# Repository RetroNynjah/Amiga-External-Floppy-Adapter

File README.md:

# Retro Ninja Amiga external floppy adapter
An adapter that allows external connection of Shugart floppy disk drives or Gotek floppy emulators

This adapter has been tested with various Amiga floppy drives and Gotek floppy emulators.
It was designed to plug directly into the external floppy port of the Amiga and connect a Gotek USB emulator with a 34-pin IDC cable and a power cable. The floppy connector on the board is rotated so a floppy cable can go in a straight loop to a Gotek laying on top of the Amiga.
It should also be possible to mount the adapter in an external case but the floppy cable would have to be turned 180 degrees to match the connectors of the board and a Gotek.

J1 is the male 23 pin D-sub connector that plugs into the external drive port on the amiga. Pretty hard to find these today but it looks like new ones will be manufactured soon.

J2 is a male header for connecting the floppy cable. Connector can be straight or right angle, open or walled depending on what you got and what you want.

J3 is for floppy power connector. Cables can be soldered directly to board if needed.

J4 is the passthrough connector for a second or third external drive.  
Connect first row of pins on header (1...23) to first row of pins on female D-sub (1...12).  
Connect second row of pins on header (2...22) to the second row of pins on female D-sub (13...23).  

This design was based on information gathered from Amiga System Programmer's Guide by Abacus and from the scematics for the A1020 drive.  
Designed using Fusion 360. Gerber files and Eagle schematics included.

This is the third version of the board. The only new functionality from earlier versions is the added power switch/jumper. Other changes are that IC1 has been changed from 74LS00 to 74LS38, the power connector has been rotated to allow a right angle connector and silkscreen has been updated.

## BOM
 |Component|Pcs |Name|Comment|
 |:--------|---:|:---|:------|
 | 74LS38 Quad NAND | 1 | IC1 | 74F38 works and 74LS03/74HCT03 seems to work too. 74LS26 and variants of it might work. 74LS00 works partially |
 | 74LS74 Flip-Flop | 1 | IC2 | 74HCT74 works fine | 
 | 100nF ceramic capacitor | 2 | C1, C2 ||
 | 1k resistor | 4 | R1, R2, R3, R4 ||
 | 12k resistor | 1 | R5 ||
 | D-sub 23M connector | 1 | J1 | D-sub This connector is pretty hard to source at the moment. Try eBay |
 | 34-pin male header | 1 | J2 | 2x17 pin 2.54mm pitch. For floppy cable IDC connector |
 | 4 pin header | 1 | J3 | 2.54mm pitch. For floppy power cable connector (or solder cables directly to board) |
 | 24-pin header | 1 | J4 | 2x12 pin 2.54mm pitch header for outgoing connection to next drive in chain. For example IDC to DB23F. D-sub 23F connectors were manufactured by Unicorns and can't be found today |
 | Jumper | 1 | JP1 | Optional jumper or connection for a power switch. If you don't need a power jumper/switch - just leave it and bridge the solder jumper SJ1 instead |

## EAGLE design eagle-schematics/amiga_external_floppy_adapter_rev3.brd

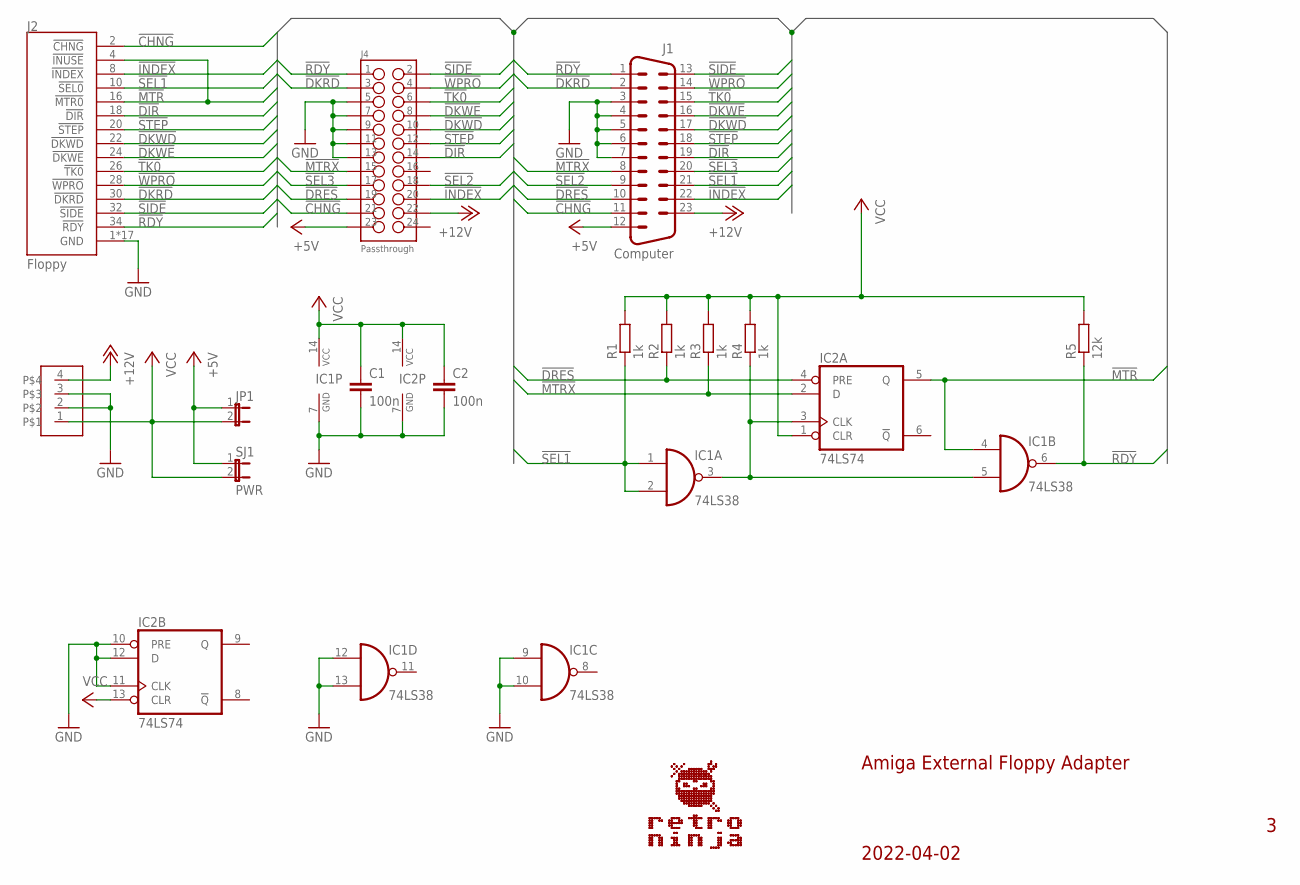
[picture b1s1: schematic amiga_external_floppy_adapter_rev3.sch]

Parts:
C1, C2: 100n; CAP_5MM_2.5X5.0_ROUND
IC1: 74LS38; DIL14
IC2: 74LS74; DIL14
J1: Computer; DSUB_M23D
J2: Floppy; HEADER_2X17_WALLED
J3: HEADER_1X4_2.50MM_RIGHT; HEADER_1X4_2.50_RIGHT
J4: Passthrough; HEADER_2X12_WALLED
JP1: JUMPER-2; HEADER_1X2
R1, R2, R3, R4: 1k; 0207/10
R5: 12k; 0207/10
SJ1: PWR; SJ-2

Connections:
!CHNG: J1.11, J2.2 (!CHNG), J4.21
!DIR: J1.19, J2.18 (!DIR), J4.14
!DKRD: J1.2, J2.30 (!DKRD), J4.3
!DKWD: J1.17, J2.22 (!DKWD), J4.10
!DKWE: J1.16, J2.24 (!DKWE), J4.8
!DRES: IC2.4 (PRE), J1.10, J4.19, R2.1
!INDEX: J1.22, J2.8 (!INDEX), J4.20
!MTR: IC1.4 (I0), IC2.5 (Q), J2.4 (!INUSE), J2.16 (!MTR0)
!MTRX: IC2.2 (D), J1.8, J4.15, R3.1
!RDY: IC1.6 (O), J1.1, J2.34 (!RDY), J4.1, R5.1
!SEL1: IC1.1 (I0), IC1.2 (I1), J1.21, J2.10 (!SEL0), R1.1
!SEL2: J1.9, J4.18
!SEL3: J1.20, J4.17
!SIDE: J1.13, J2.32 (!SIDE), J4.2
!STEP: J1.18, J2.20 (!STEP), J4.12
!TK0: J1.15, J2.26 (!TK0), J4.6
!WPRO: J1.14, J2.28 (!WPRO), J4.4
+5V: J1.12, J4.23, JP1.1, SJ1.1
+12V: J1.23, J3.4, J4.22
GND: C1.2, C2.2, IC1.7 (GND), IC1.9 (I0), IC1.10 (I1), IC1.12 (I0), IC1.13 (I1), IC2.7 (GND), IC2.10 (PRE), IC2.11 (CLK), IC2.12 (D), J1.3, J1.4, J1.5, J1.6, J1.7, J2.1 (GND), J2.3 (GND), J2.5 (GND), J2.7 (GND), J2.9 (GND), J2.11 (GND), J2.13 (GND), J2.15 (GND), J2.17 (GND), J2.19 (GND), J2.21 (GND), J2.23 (GND), J2.25 (GND), J2.27 (GND), J2.29 (GND), J2.31 (GND), J2.33 (GND), J3.2, J3.3, J4.5, J4.7, J4.9, J4.11, J4.13
unnamed: IC1.3 (O), IC1.5 (I1), IC2.3 (CLK), R4.1
VCC: C1.1, C2.1, IC1.14 (VCC), IC2.1 (CLR), IC2.13 (CLR), IC2.14 (VCC), J3.1, JP1.2, R1.2, R2.2, R3.2, R4.2, R5.2, SJ1.2

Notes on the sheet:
2022-04-02
Amiga External Floppy Adapter

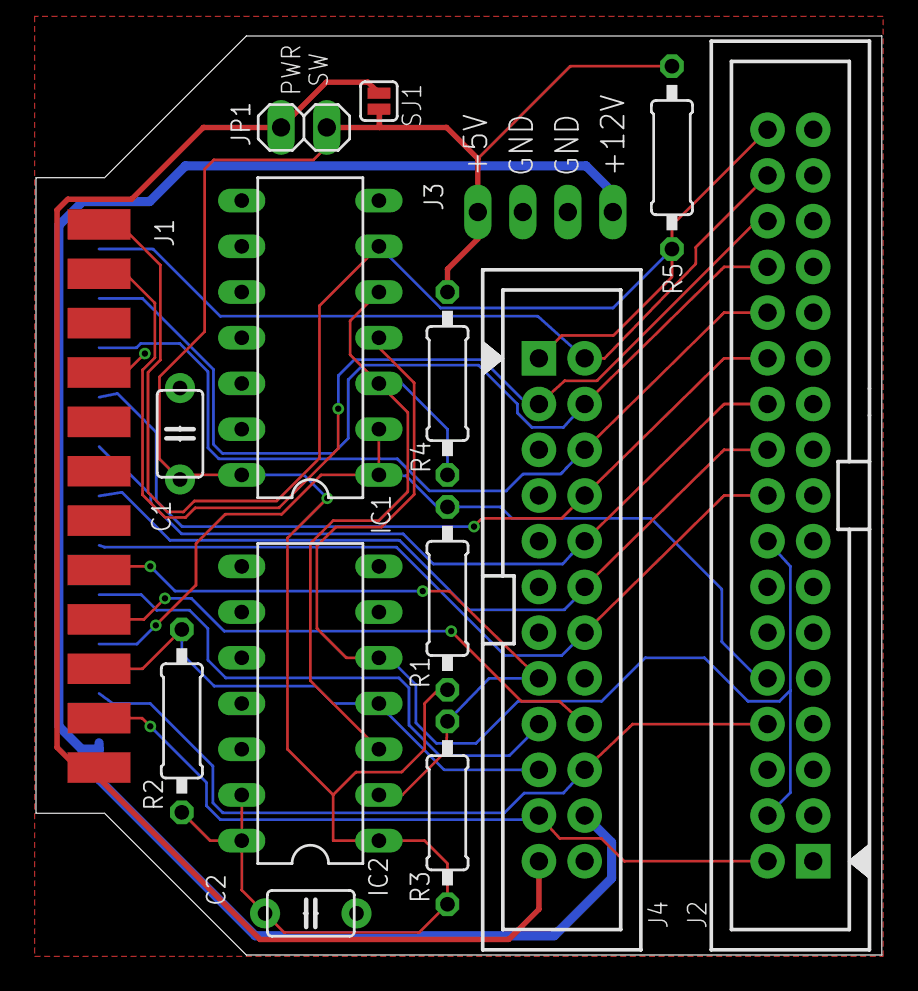
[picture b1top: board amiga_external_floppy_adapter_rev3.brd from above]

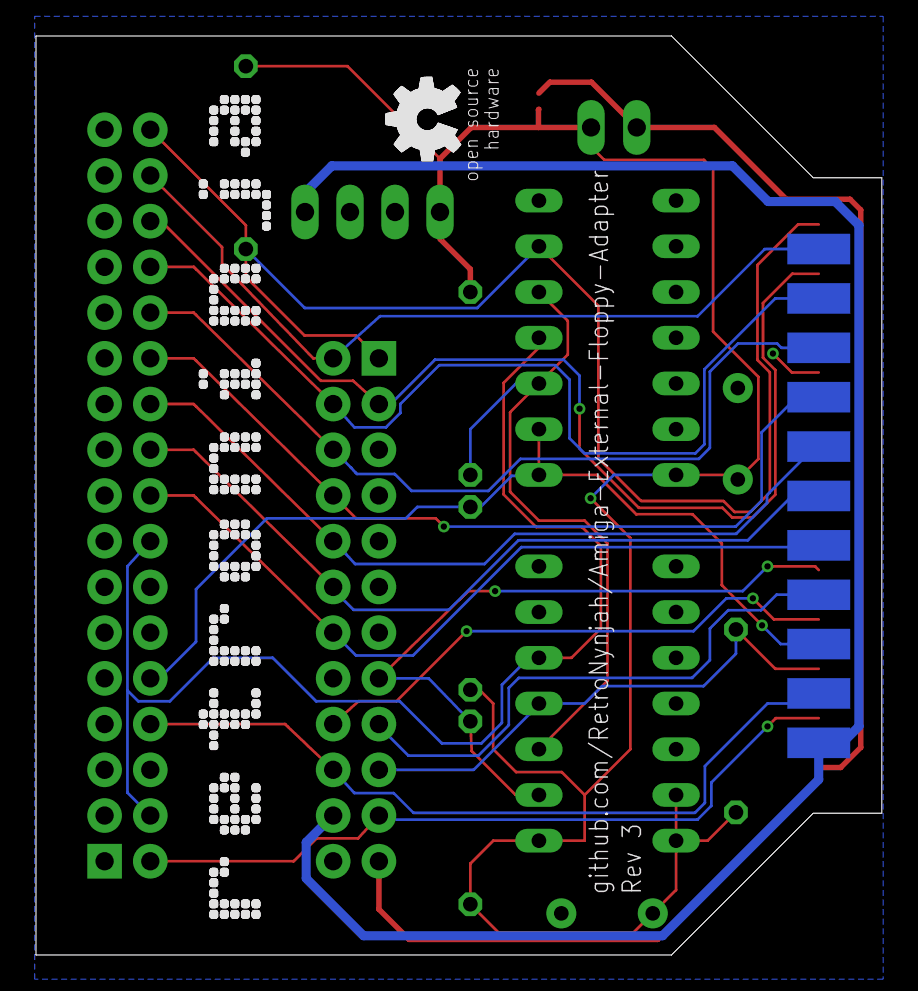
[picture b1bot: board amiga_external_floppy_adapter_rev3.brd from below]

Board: 2 copper layers, 47.0 x 51.1 mm, 17 parts (2 on the bottom side), 22 nets.

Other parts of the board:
U$1: RETRONINJA_WORD_46X4
U$2: OSHW_5MM

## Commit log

2020-07-02 First version
2020-07-02 Minor adjustment
2020-07-02 new render
2020-07-02 Added Schematics as PDF
2020-07-03 Updated layout
2020-08-01 Added license
2022-04-02 Update rev1_gerbers.zip
    Restore original Rev 1 gerbers
2022-04-02 Rev 3
